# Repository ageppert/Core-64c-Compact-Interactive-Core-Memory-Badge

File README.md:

# Core-64c-Compact-Interactive-Core-Memory-Badge
Weave your own 64 bits of core memory over the top of LEDs to interact with directly using a magnetic wand.

Purchase: https://www.Core64.io

Follow this project at: https://hackaday.io/project/166155-core-64-interactive-core-memory-badge

You are in the hardware development repository. Production version firmware is at https://github.com/ageppert/Core64/

# Hardware Version History (latest on top)

HWV 0.3.0 Correct shift register schematic, add TC0_MON as ADC3, move 5V0 cap down, alternate LDO v-regs with 0.1uF caps, rotate SPI GPIO 180°, matrix current setting resistors 6.8 Ohm, I2C pull-ups 1.2K, add battery pack wire pads directly to board, silkscreen tweaks, move LED Matrix Driver components away from lanyard hole.

HWV 0.2.1 Rework HWV 0.2.0 to correct shift register schematics mistakes.

HWV 0.2.0 Change to 74HC595 shift registers for IO expansion. First version prototyped. Matrix current setting resistors 5.1 Ohm.

HWV 0.1.0 Compact Triple Stack - use 74HC138/238 3-to-8 decoders for IO expansion. Abandoned before prototyping.

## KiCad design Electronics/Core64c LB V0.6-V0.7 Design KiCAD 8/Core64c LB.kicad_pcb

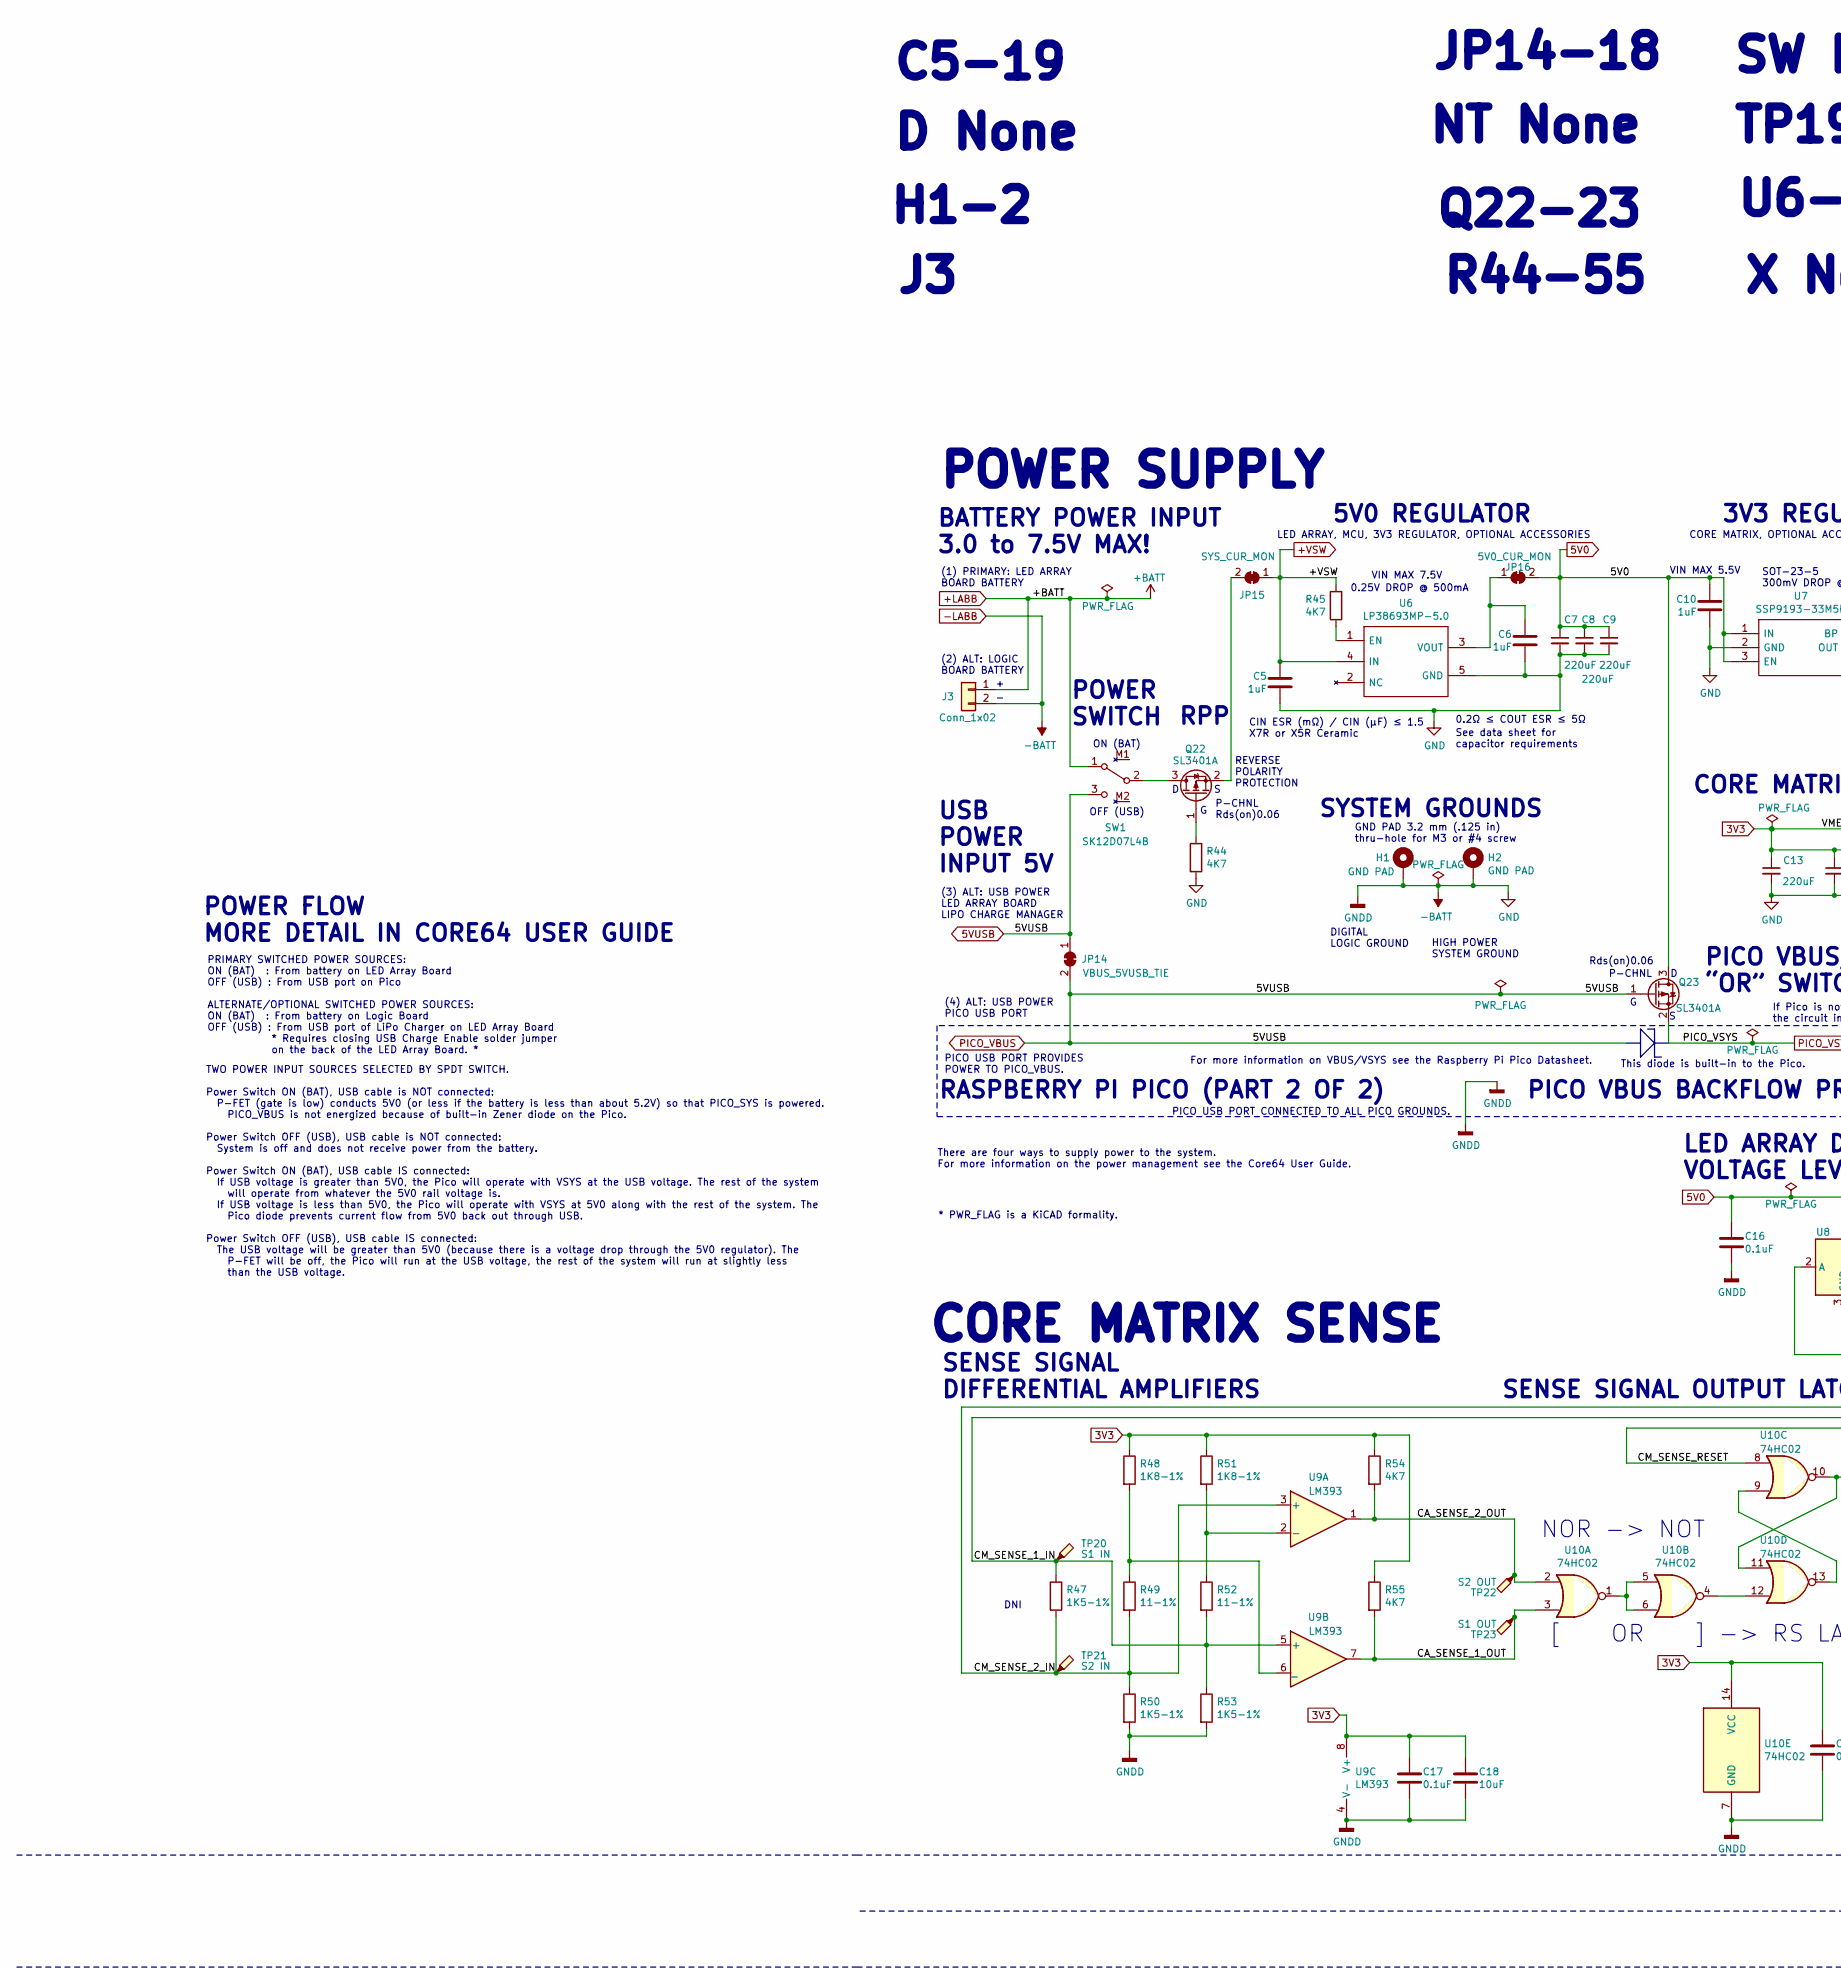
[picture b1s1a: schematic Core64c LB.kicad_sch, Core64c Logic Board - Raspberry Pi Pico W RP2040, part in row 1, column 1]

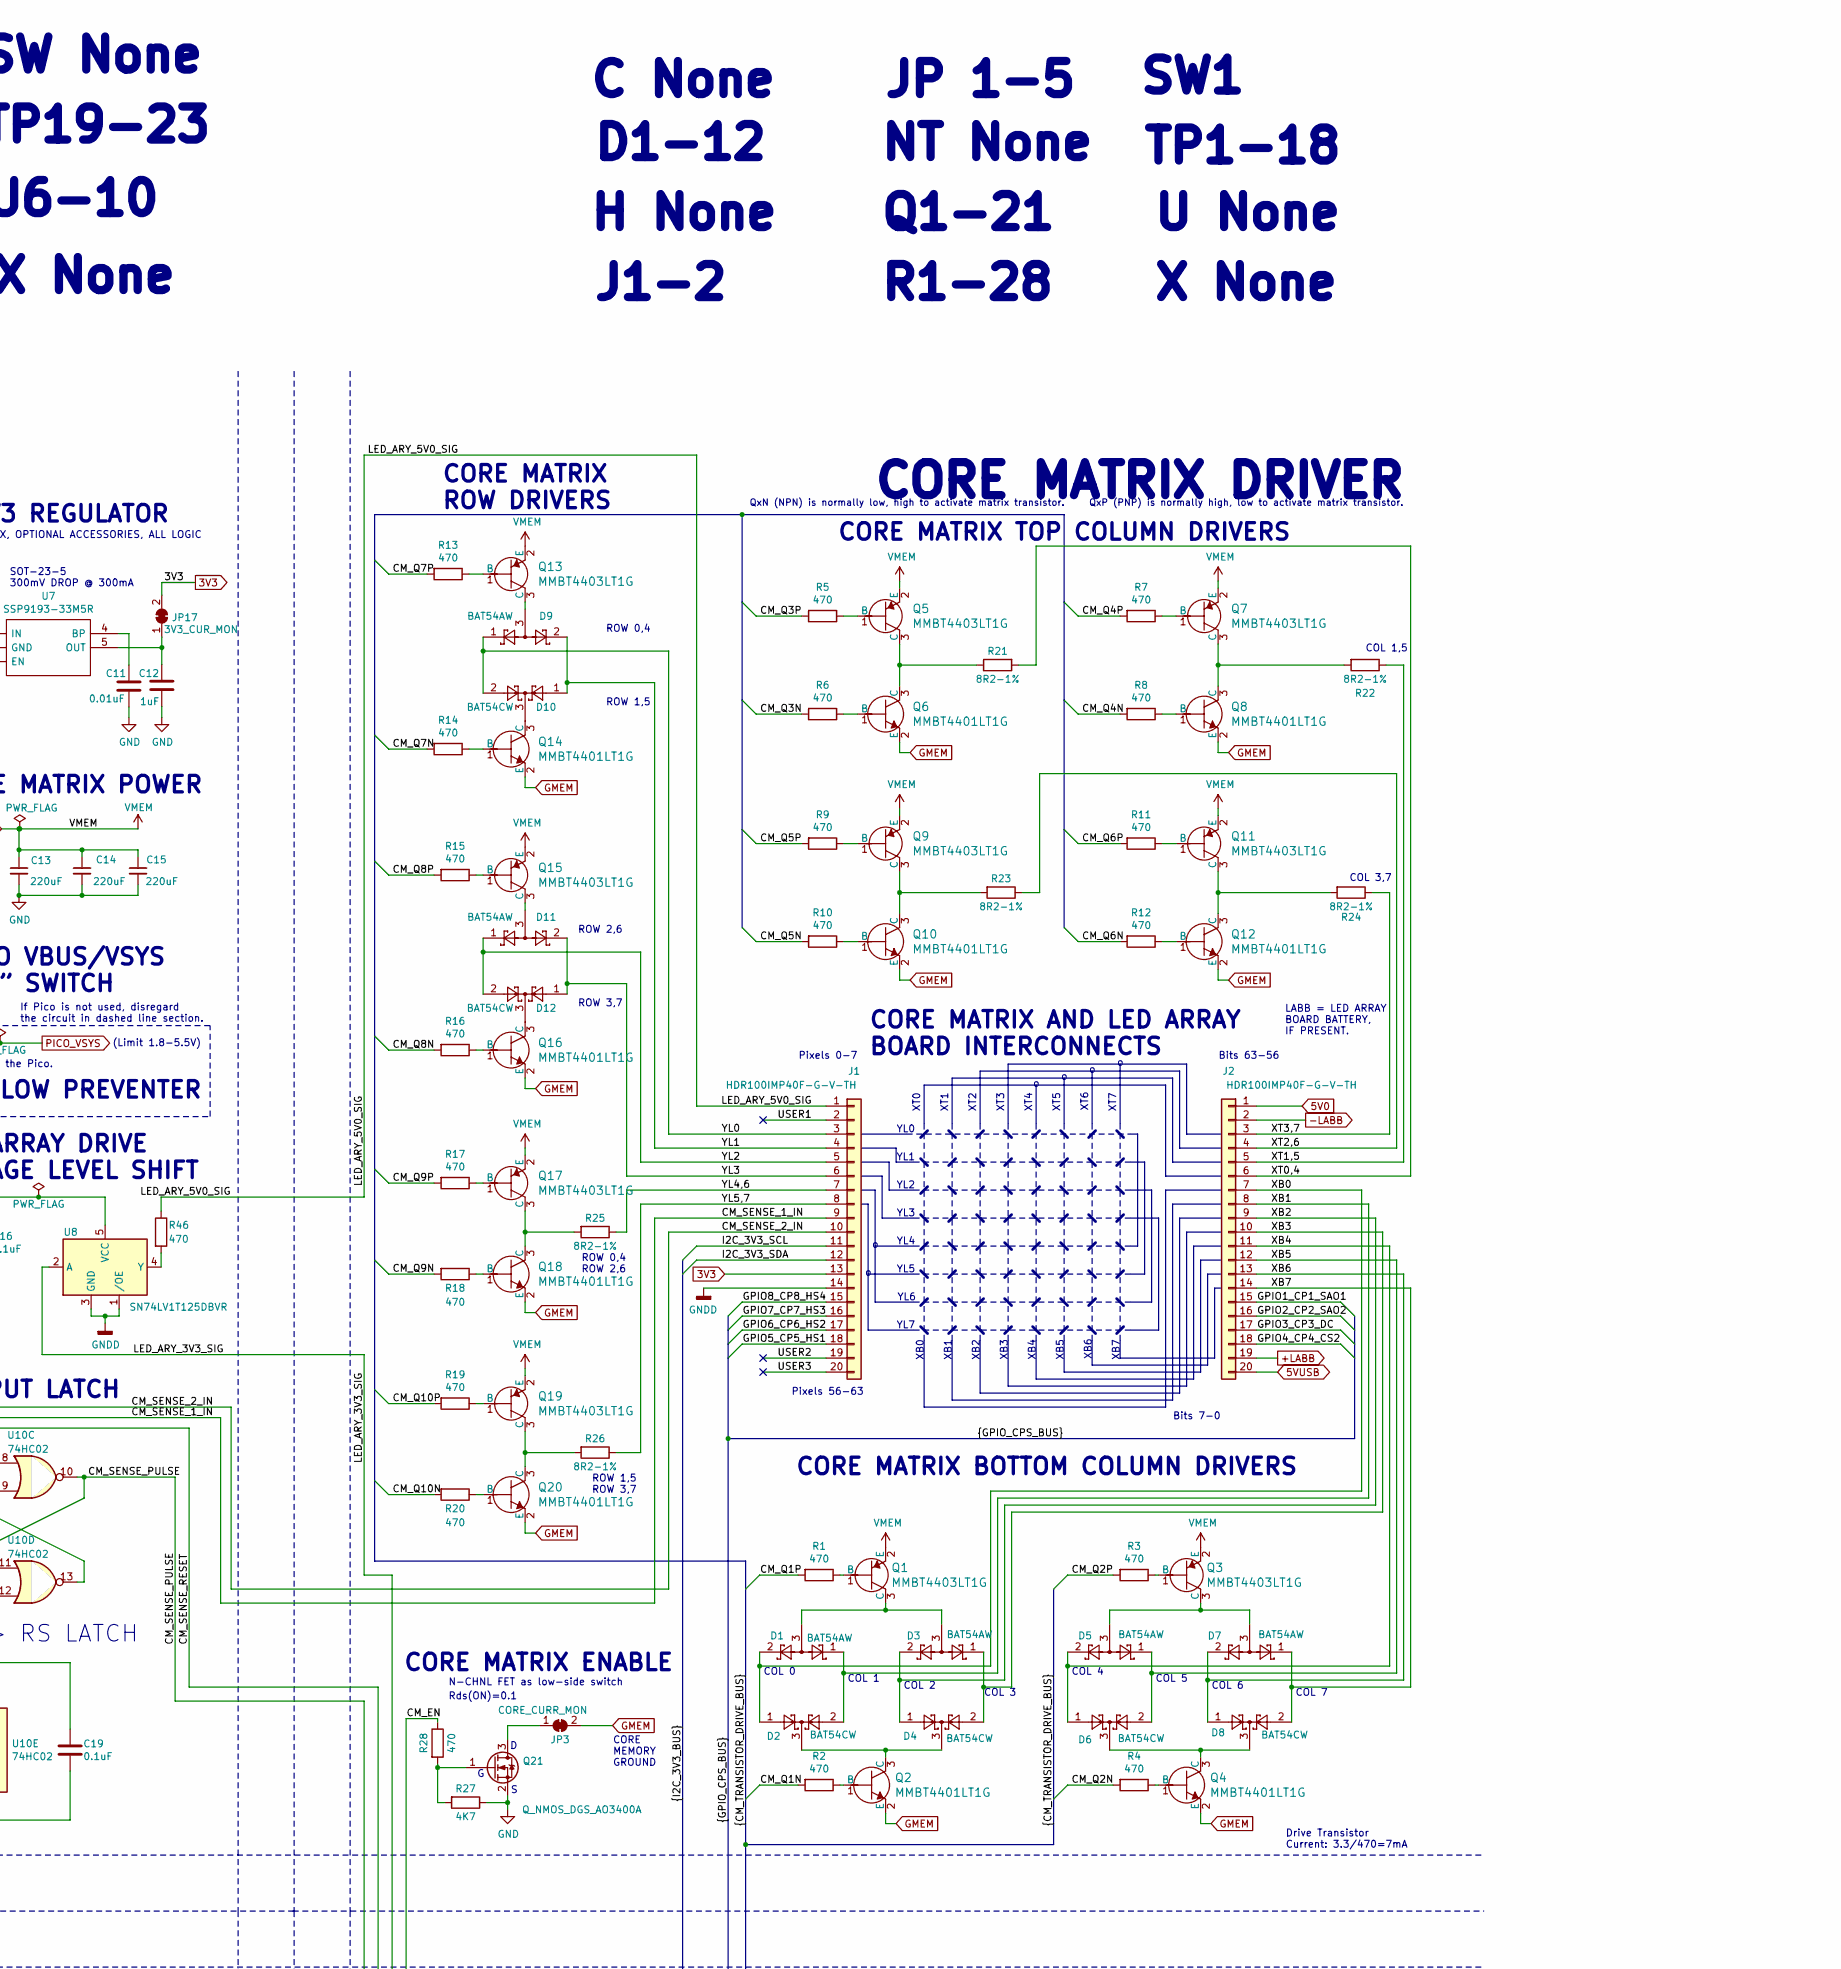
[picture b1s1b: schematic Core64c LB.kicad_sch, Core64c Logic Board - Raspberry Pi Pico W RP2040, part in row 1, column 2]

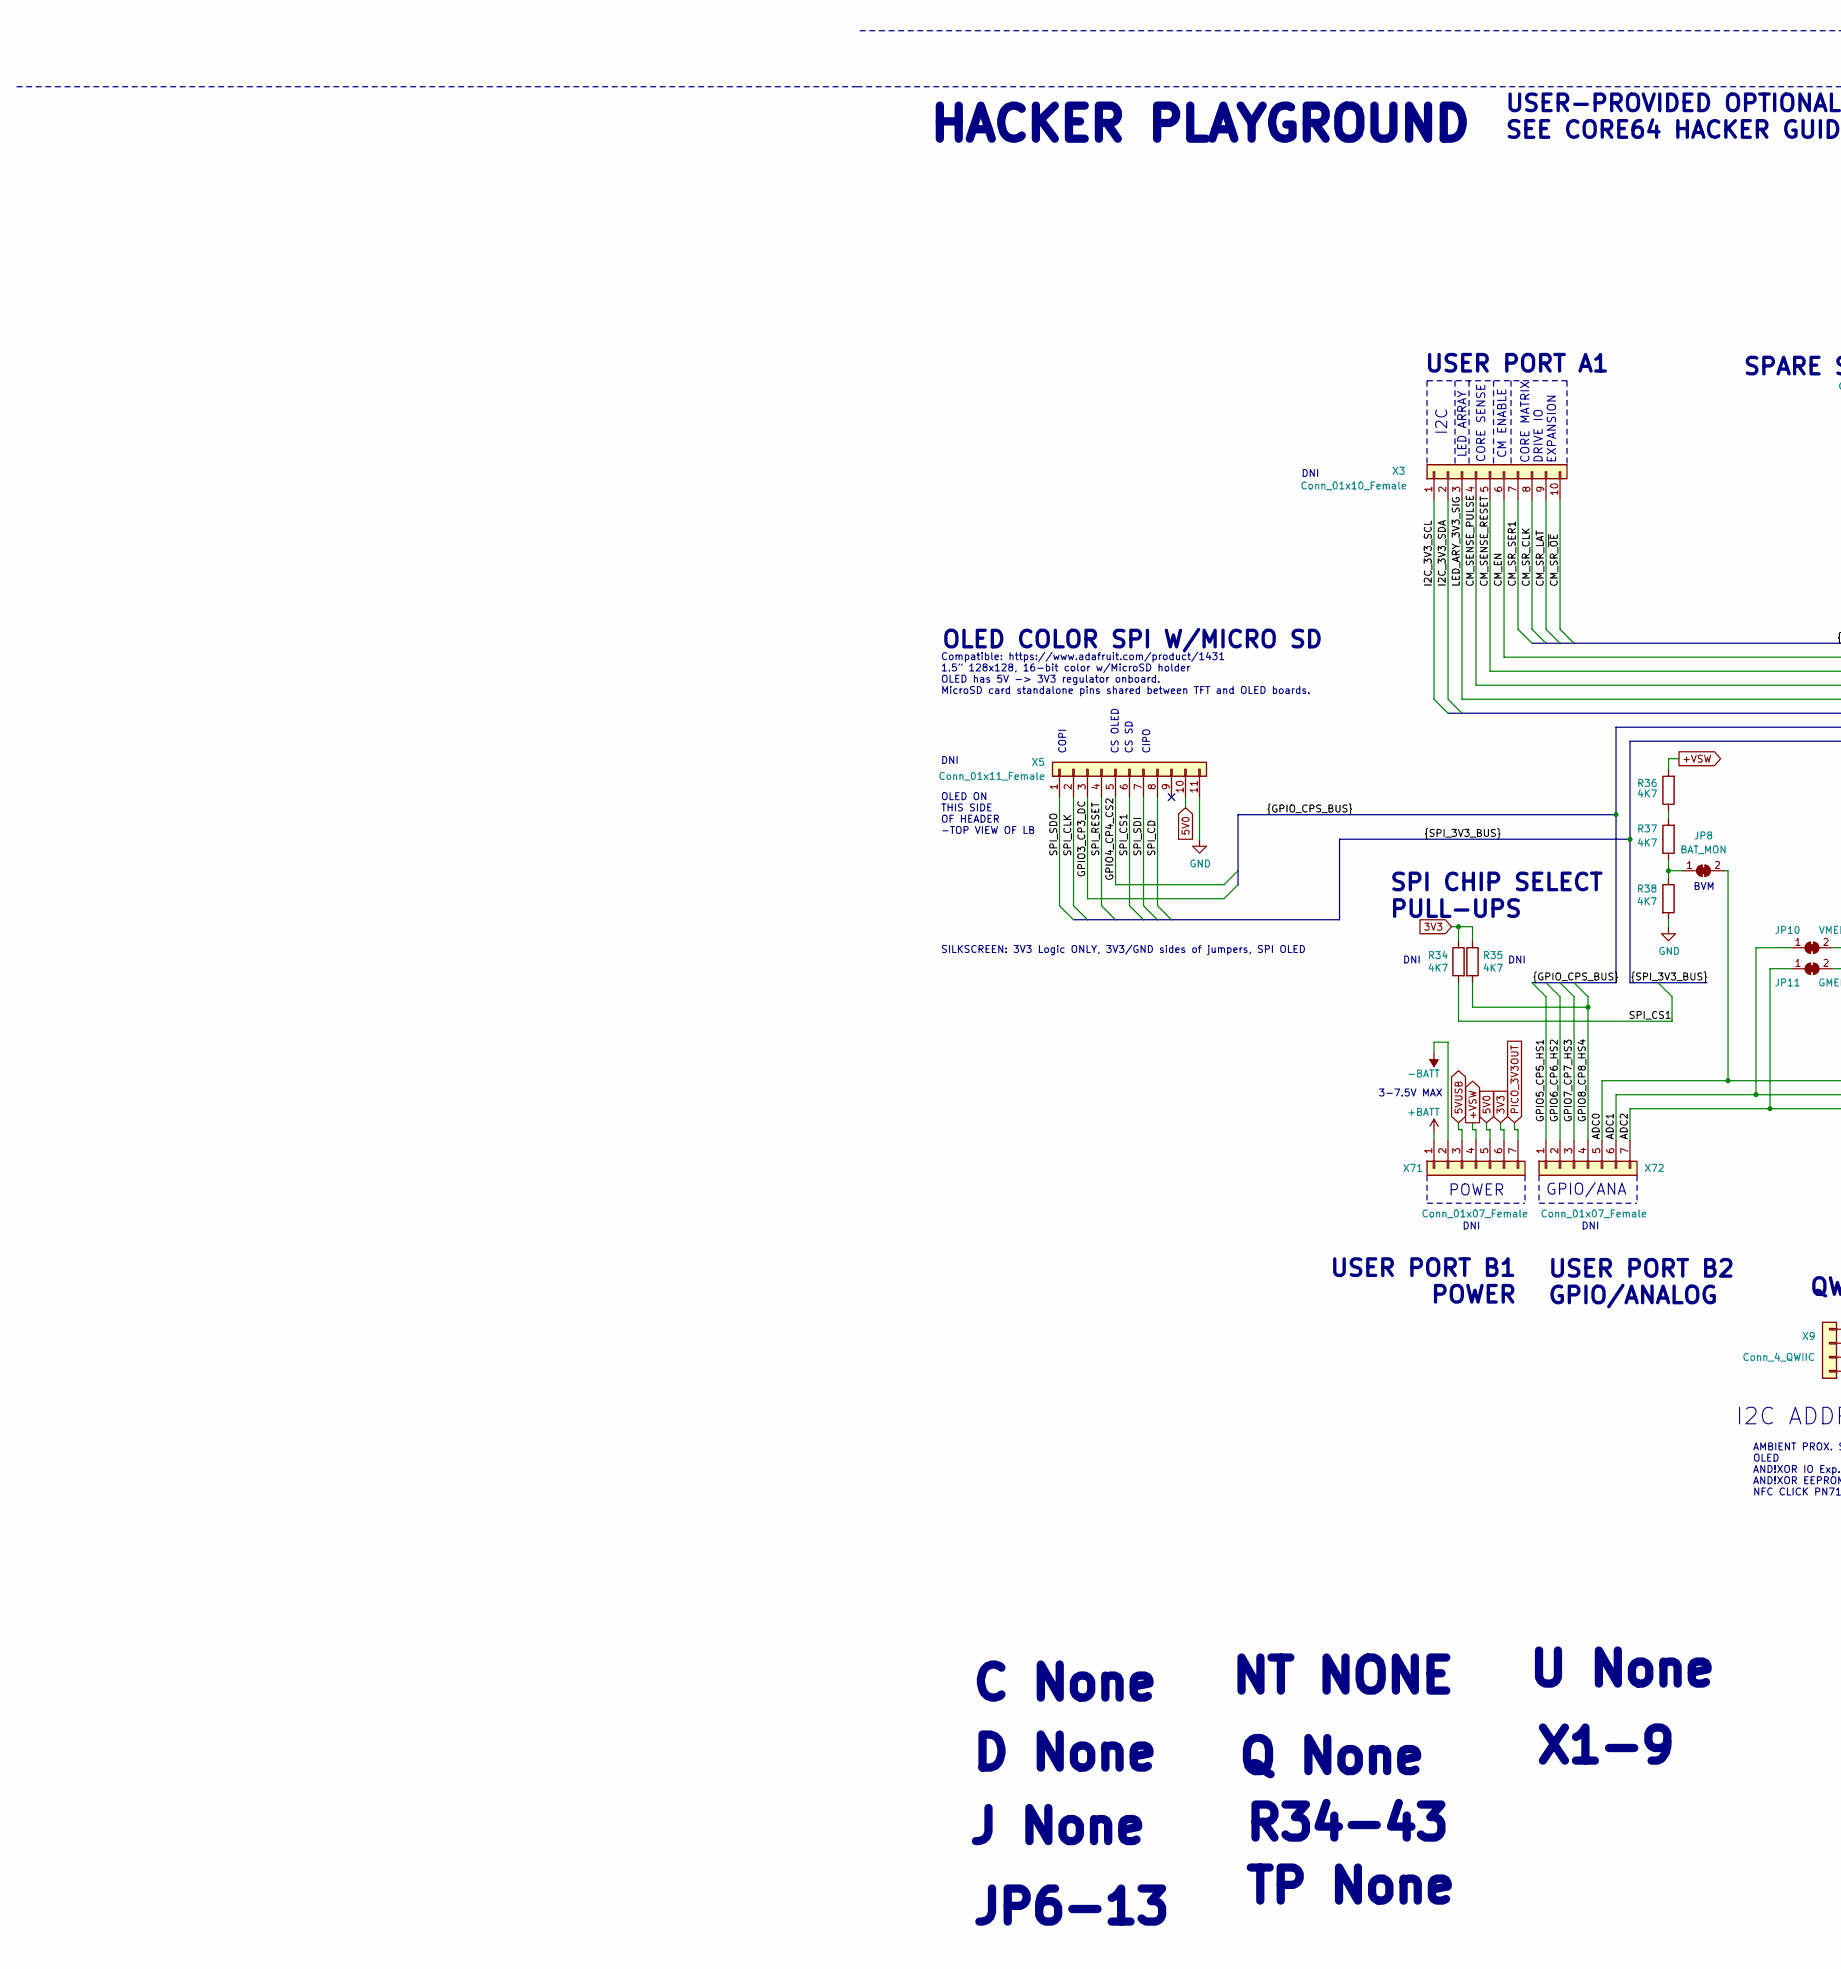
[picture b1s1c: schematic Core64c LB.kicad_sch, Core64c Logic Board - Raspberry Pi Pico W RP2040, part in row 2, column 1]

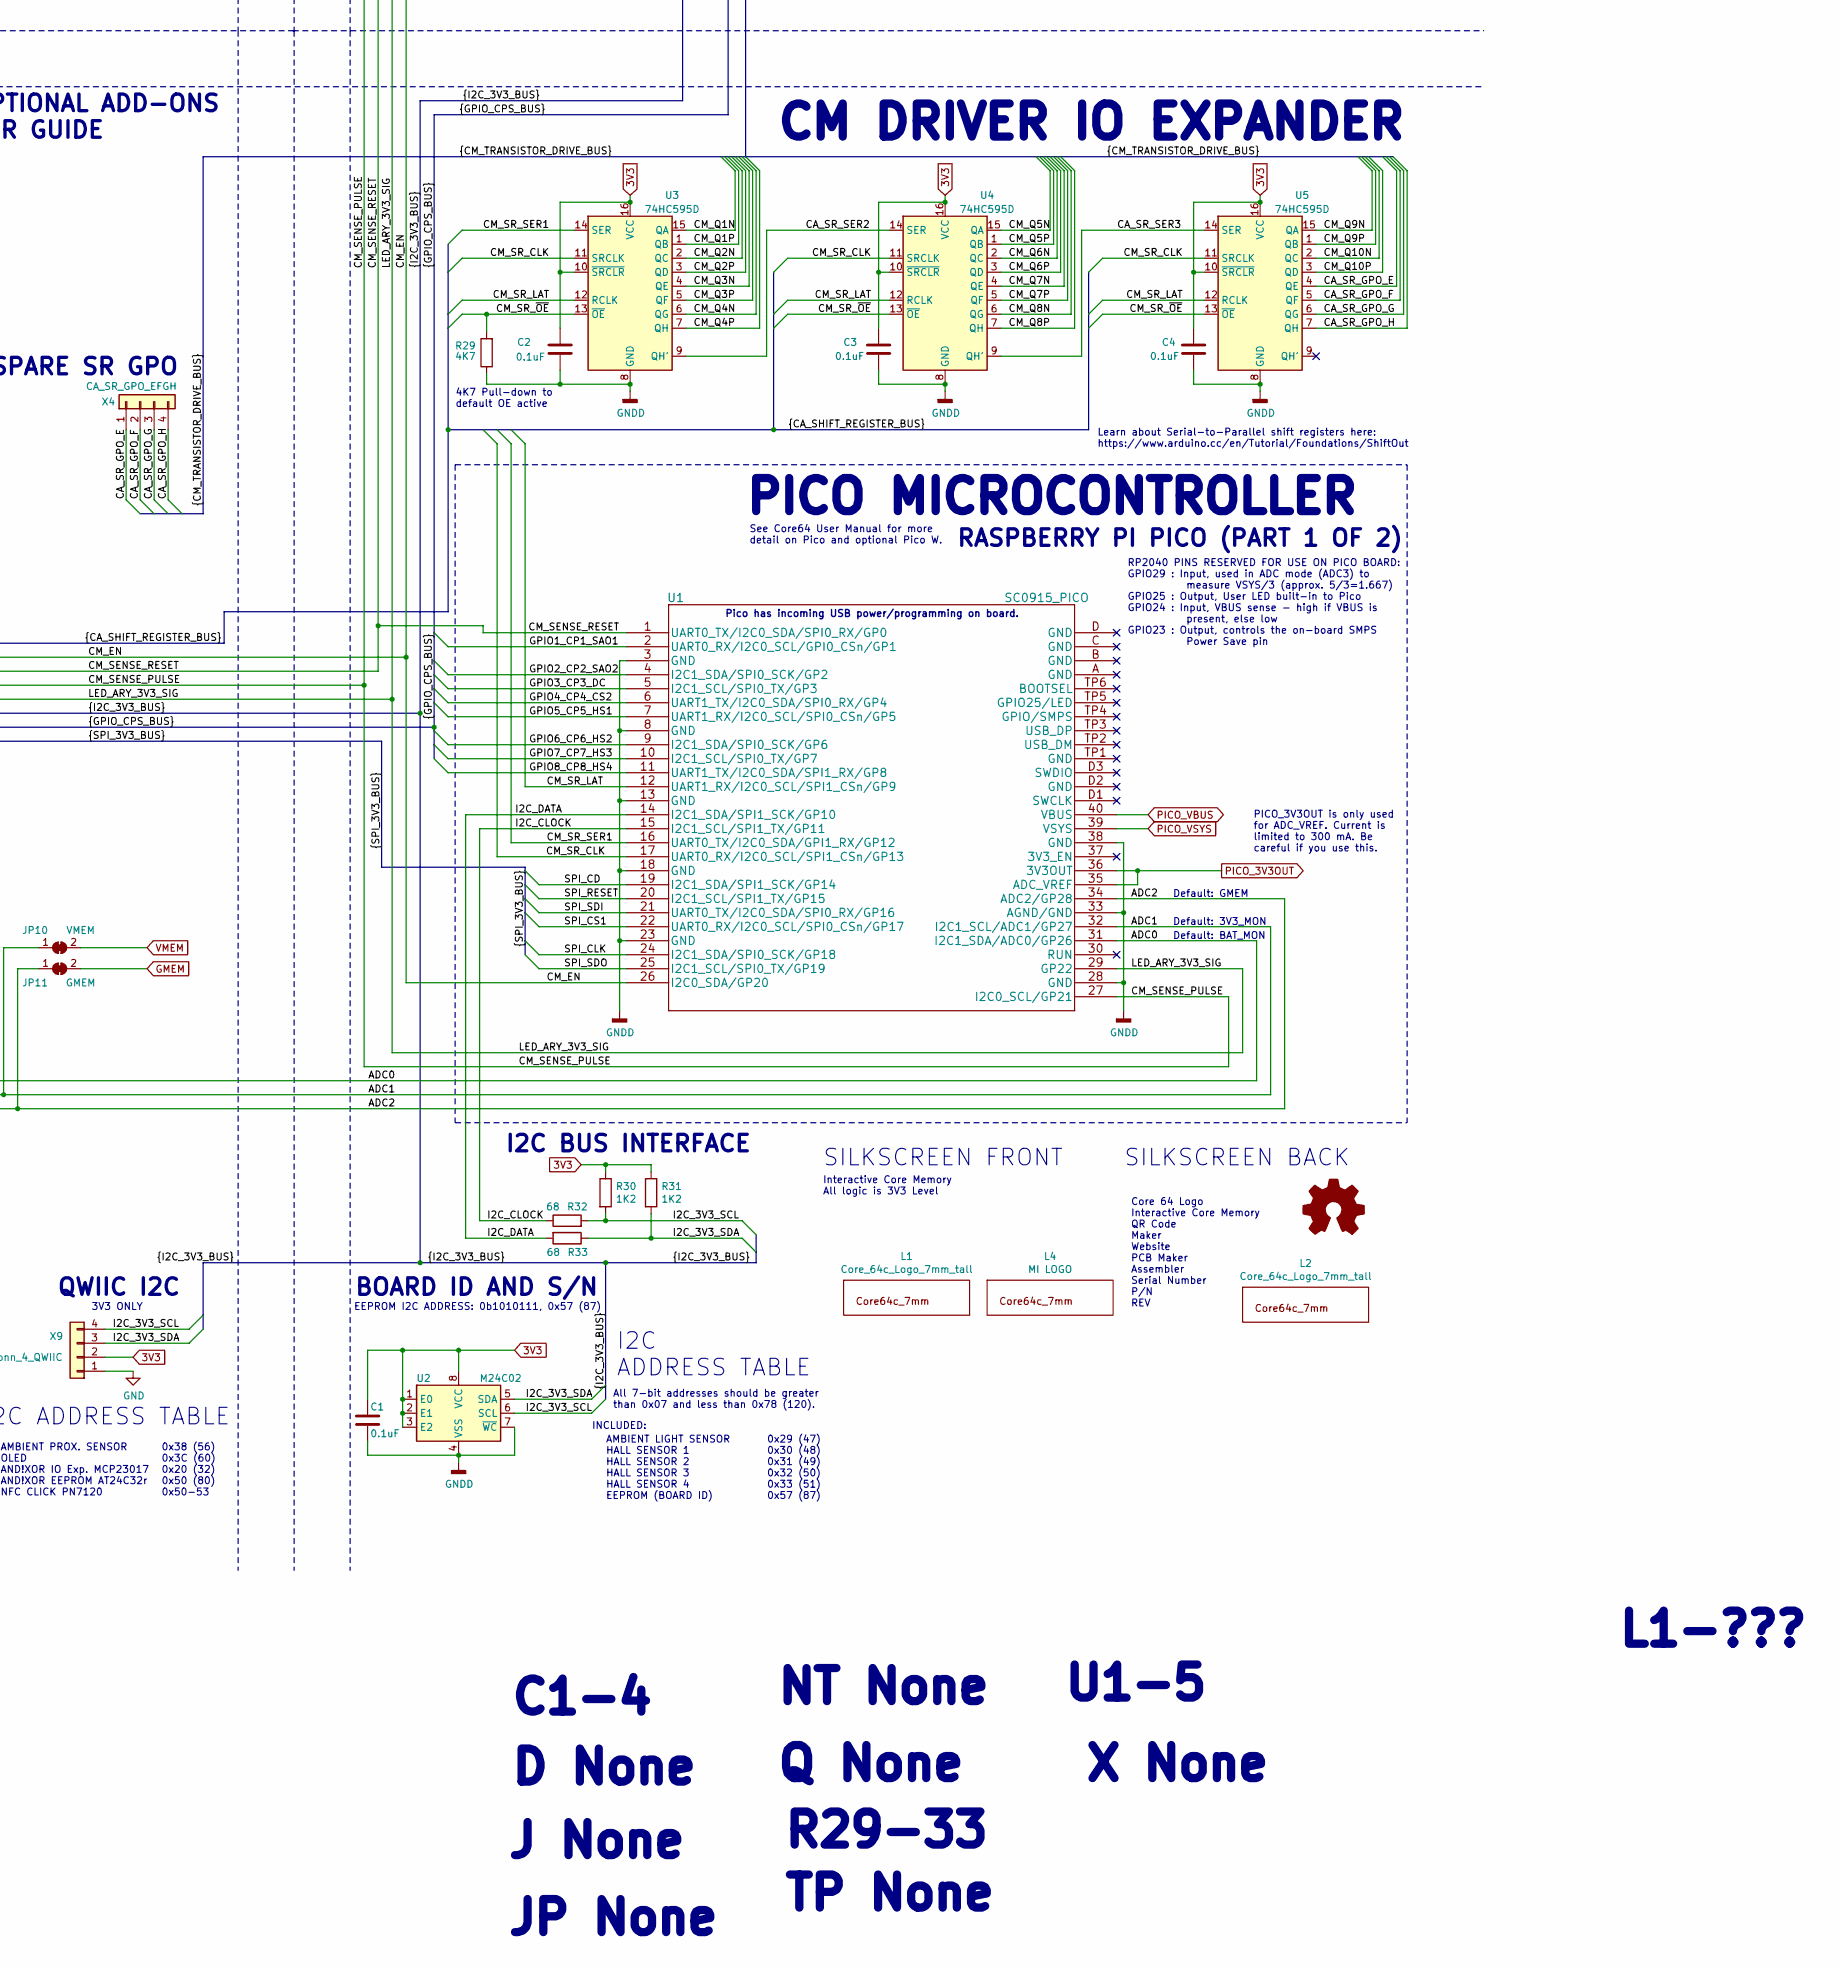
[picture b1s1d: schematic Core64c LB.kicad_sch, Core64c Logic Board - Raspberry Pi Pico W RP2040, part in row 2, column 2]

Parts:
C1, C2, C3, C4, C16, C17, C19: 0.1uF; C_0805_2012Metric; LCSC C28233
C5, C6, C10, C12: 1uF; C_0805_2012Metric; LCSC C28323
C7, C8, C9, C13, C14, C15: 220uF; C_1206_3216Metric; LCSC C412252
C11: 0.01uF; C_0805_2012Metric; LCSC C1710
C18: 10uF; C_0805_2012Metric; LCSC C17024
D1, D3, D5, D7, D9, D11: BAT54AW; SOT-323_SC-70; LCSC C78261
D2, D4, D6, D8, D10, D12: BAT54CW; SOT-323_SC-70; LCSC C83573
H1, H2: GND PAD; MountingHole_3.2mm_M3_Pad_Via
J1, J2: HDR100IMP40F-G-V-TH; PinSocket_1x20_P2.54mm_Vertical
J3: Conn_1x02; PinSocket_1x02_P2.54mm_Vertical
JP3: CORE_CURR_MON; SolderJumper-2_P1.3mm_Bridged_RoundedPad1.0x1.5mm
JP8: BAT_MON; SolderJumper-2_P1.3mm_Bridged_RoundedPad1.0x1.5mm
JP10: VMEM; SolderJumper-2_P1.3mm_Bridged_RoundedPad1.0x1.5mm
JP11: GMEM; SolderJumper-2_P1.3mm_Bridged_RoundedPad1.0x1.5mm
JP14: VBUS_5VUSB_TIE; SolderJumper-2_P1.3mm_Bridged_RoundedPad1.0x1.5mm
JP15: SYS_CUR_MON; SolderJumper-2_P1.3mm_Bridged_RoundedPad1.0x1.5mm
JP16: 5V0_CUR_MON; SolderJumper-2_P1.3mm_Bridged_RoundedPad1.0x1.5mm
JP17: 3V3_CUR_MON; SolderJumper-2_P1.3mm_Bridged_RoundedPad1.0x1.5mm
L1, L2: Core_64c_Logo_7mm_tall; Core64c_Logo_7mm
L3: Logo_Open_Hardware_Small; OSHW-Logo2_9.8x8mm_SilkScreen
L4: MI LOGO; Machine_Ideas_logo_1
Q1, Q3, Q5, Q7, Q9, Q11, Q13, Q15, Q17, Q19: MMBT4403LT1G; SOT-23-3; MPN MMBT4403LT1G; LCSC C78864
Q2, Q4, Q6, Q8, Q10, Q12, Q14, Q16, Q18, Q20: MMBT4401LT1G; SOT-23-3; MPN MMBT4401LT1G; LCSC C31776
Q21: Q_NMOS_DGS_AO3400A; SOT-23-3; LCSC C20917
Q22, Q23: SL3401A; SOT-23-3; LCSC C350311
R1, R2, R3, R4, R5, R6, R7, R8, R9, R10, R11, R12, R13, R14, R15, R16, R17, R18, R19, R20, R28, R46: 470; R_0805_2012Metric; LCSC C17710
R21, R22, R23, R24, R25, R26: 8R2-1%; R_0805_2012Metric; LCSC C17830
R27, R29, R34, R35, R36, R37, R38, R44, R45, R54, R55: 4K7; R_0805_2012Metric; LCSC C17673
R30, R31: 1K2; R_0805_2012Metric; LCSC C17379
R32, R33: 68; R_0805_2012Metric; LCSC C17802
R47, R50, R53: 1K5-1%; R_0805_2012Metric; LCSC C4310
R48, R51: 1K8-1%; R_0805_2012Metric; LCSC C17398
R49, R52: 11-1%; R_0805_2012Metric; LCSC C17430
SW1: SK12D07L4B; SK12D07VG4; LCSC C480340
TP20: S1 IN; TestPoint_THTPad_D1.5mm_Drill1.0mm
TP21: S2 IN; TestPoint_THTPad_D1.5mm_Drill1.0mm
TP22: S2 OUT; TestPoint_THTPad_D1.5mm_Drill1.0mm
TP23: S1 OUT; TestPoint_THTPad_D1.5mm_Drill1.0mm
U1: SC0915_PICO; Pico_W_SC0915
U2: M24C02; SOIC-8_3.9x4.9mm_P1.27mm; LCSC C7562
U3, U4, U5: 74HC595D; SOIC-16_W3.90mm; MPN SN74HC595DR; LCSC C5947
U6: LP38693MP-5.0; SOT-223-5; Manufacturer_Part_Number LP38693MP-5.0; Mouser Part Number LP38693MP-5.0
U7: SSP9193-33M5R; SOT-23-5; Manufacturer_Part_Number SGM2007-3.3XN5/TR; Mouser Part Number SGM2007-3.3XN5/TR
U8: SN74LV1T125DBVR; SOT-23-5; LCSC C473338
U9: LM393; SOIC-8_W3.9mm; LCSC C7955
U10: 74HC02; SOIC-14_3.9x8.7mm_P1.27mm; LCSC C350559
X3: Conn_01x10_Female; PinSocket_1x10_P2.54mm_Vertical
X4: CA_SR_GPO_EFGH; PinSocket_1x04_P2.54mm_Vertical
X5: Conn_01x11_Female; PinSocket_1x11_P2.54mm_Vertical
X9: Conn_4_QWIIC; JST_SH_SM04B-SRSS-TB_1x04-1MP_P1.00mm_Horizontal; MPN SM04B-SRSS-TB(LF)(SN); Digi-Key_PN 455-1804-1-ND
X71, X72: Conn_01x07_Female; PinSocket_1x07_P2.54mm_Vertical

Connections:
3V3: C1.1, C2.1, C3.1, C4.1, C13.1, C14.1, C15.1, C17.1, C18.1, C19.1, J1.13, JP10.2 (B), JP17.2 (B), Q1.2 (E), Q3.2 (E), Q5.2 (E), Q7.2 (E), Q9.2 (E), Q11.2 (E), Q13.2 (E), Q15.2 (E), Q17.2 (E), Q19.2 (E), R30.1, R31.1, R34.1, R35.1, R48.1, R51.1, R54.1, R55.1, U2.1 (E0), U2.2 (E1), U2.3 (E2), U2.8 (VCC), U3.10 (~SRCLR), U3.16 (VCC), U4.10 (~SRCLR), U4.16 (VCC), U5.10 (~SRCLR), U5.16 (VCC), U9.8 (V+), U10.14 (VCC), X9.2, X71.6
5V0: C7.1, C8.1, C9.1, C10.1, C16.1, J2.1, JP16.2 (B), Q23.3 (D), U7.1 (IN), U7.3 (EN), U8.5 (VCC), X5.10, X71.5
5VUSB: J2.20, JP14.1 (A), JP14.2 (B), Q23.1 (G), SW1.3 (C), U1.40 (VBUS), X71.3
+LABB: J2.19, J3.1, SW1.1 (A), X71.1
+VSW: C5.1, JP15.1 (A), R36.2, R45.1, U6.4 (IN), X71.4
-LABB: C1.2, C2.2, C3.2, C4.2, C5.2, C6.2, C7.2, C8.2, C9.2, C10.2, C11.2, C12.2, C13.2, C14.2, C15.2, C16.2, C17.2, C18.2, C19.2, H1.1, H2.1, J1.14, J2.2, J3.2, Q21.2 (S), R27.1, R29.1, R38.2, R44.2, R50.2, R53.2, U1.3 (GND), U1.8 (GND), U1.13 (GND), U1.18 (GND), U1.23 (GND), U1.28 (GND), U1.33 (AGND/GND), U1.38 (GND), U2.4 (VSS), U2.7 (~WC), U3.8 (GND), U4.8 (GND), U5.8 (GND), U6.5 (GND), U7.2 (GND), U8.1 (/OE), U8.3 (GND), U9.4 (V-), U10.7 (GND), X5.11, X9.1, X71.2
/ADC0: JP8.2 (B), U1.31 (I2C1_SDA/ADC0/GP26), X72.5
/ADC1: JP10.1 (A), U1.32 (I2C1_SCL/ADC1/GP27), X72.6
/ADC2: JP11.1 (A), U1.34 (ADC2/GP28), X72.7
/CA_SENSE_1_OUT: R55.2, TP23.1, U9.7, U10.3
/CA_SENSE_2_OUT: R54.2, TP22.1, U9.1, U10.2
/CA_SR_GPO_E: U5.4 (QE), X4.1
/CA_SR_GPO_F: U5.5 (QF), X4.2
/CA_SR_GPO_G: U5.6 (QG), X4.3
/CA_SR_GPO_H: U5.7 (QH), X4.4
/CA_SR_SER2: U3.9 (QH'), U4.14 (SER)
/CA_SR_SER3: U4.9 (QH'), U5.14 (SER)
/CM_EN: R28.1, U1.26 (I2C0_SDA/GP20), X3.6
/CM_Q1N: R2.2, U3.15 (QA)
/CM_Q1P: R1.2, U3.1 (QB)
/CM_Q2N: R4.2, U3.2 (QC)
/CM_Q2P: R3.2, U3.3 (QD)
/CM_Q3N: R6.2, U3.4 (QE)
/CM_Q3P: R5.2, U3.5 (QF)
/CM_Q4N: R8.2, U3.6 (QG)
/CM_Q4P: R7.2, U3.7 (QH)
/CM_Q5N: R10.2, U4.15 (QA)
/CM_Q5P: R9.2, U4.1 (QB)
/CM_Q6N: R12.2, U4.2 (QC)
/CM_Q6P: R11.2, U4.3 (QD)
/CM_Q7N: R14.2, U4.4 (QE)
/CM_Q7P: R13.2, U4.5 (QF)
/CM_Q8N: R16.2, U4.6 (QG)
/CM_Q8P: R15.2, U4.7 (QH)
/CM_Q9N: R18.2, U5.15 (QA)
/CM_Q9P: R17.2, U5.1 (QB)
/CM_Q10N: R20.2, U5.2 (QC)
/CM_Q10P: R19.2, U5.3 (QD)
/CM_SENSE_1_IN: J1.9, R47.1, R52.2, R53.1, TP20.1, U9.5 (+)
/CM_SENSE_2_IN: J1.10, R47.2, R49.2, R50.1, TP21.1, U9.3 (+)
/CM_SENSE_PULSE: U1.27 (I2C0_SCL/GP21), U10.10, U10.11, X3.4
/CM_SENSE_RESET: U1.1 (UART0_TX/I2C0_SDA/SPI0_RX/GP0), U10.8, X3.5
/CM_SR_CLK: U1.17 (UART0_RX/I2C0_SCL/SPI1_CSn/GP13), U3.11 (SRCLK), U4.11 (SRCLK), U5.11 (SRCLK), X3.8
/CM_SR_LAT: U1.12 (UART1_RX/I2C0_SCL/SPI1_CSn/GP9), U3.12 (RCLK), U4.12 (RCLK), U5.12 (RCLK), X3.9
/CM_SR_SER1: U1.16 (UART0_TX/I2C0_SDA/GPI1_RX/GP12), U3.14 (SER), X3.7
/CM_SR_~OE: R29.2, U3.13 (~OE), U4.13 (~OE), U5.13 (~OE), X3.10
/GPIO1_CP1_SAO1: J2.15, U1.2 (UART0_RX/I2C0_SCL/GPI0_CSn/GP1)
/GPIO2_CP2_SAO2: J2.16, U1.4 (I2C1_SDA/SPI0_SCK/GP2)
/GPIO3_CP3_DC: J2.17, U1.5 (I2C1_SCL/SPI0_TX/GP3), X5.3
/GPIO4_CP4_CS2: J2.18, U1.6 (UART1_TX/I2C0_SDA/SPI0_RX/GP4), X5.5
/GPIO5_CP5_HS1: J1.18, U1.7 (UART1_RX/I2C0_SCL/SPI0_CSn/GP5), X72.1
/GPIO6_CP6_HS2: J1.17, U1.9 (I2C1_SDA/SPI0_SCK/GP6), X72.2
/GPIO7_CP7_HS3: J1.16, U1.10 (I2C1_SCL/SPI0_TX/GP7), X72.3
/GPIO8_CP8_HS4: J1.15, R35.2, U1.11 (UART1_TX/I2C0_SDA/SPI1_RX/GP8), X72.4
/I2C_3V3_SCL: J1.11, R30.2, R32.2, U2.6 (SCL), X3.1, X9.4
/I2C_3V3_SDA: J1.12, R31.2, R33.1, U2.5 (SDA), X3.2, X9.3
/I2C_CLOCK: R32.1, U1.15 (I2C1_SCL/SPI1_TX/GP11)
/I2C_DATA: R33.2, U1.14 (I2C1_SDA/SPI1_SCK/GP10)
/LED_ARY_3V3_SIG: U1.29 (GP22), U8.2 (A), X3.3
/LED_ARY_5V0_SIG: J1.1, R46.1
/SPI_CD: U1.19 (I2C1_SDA/SPI1_SCK/GP14), X5.8
/SPI_CLK: U1.24 (I2C1_SDA/SPI0_SCK/GP18), X5.2
/SPI_CS1: R34.2, U1.22 (UART0_RX/I2C0_SCL/SPI0_CSn/GP17), X5.6
/SPI_RESET: U1.20 (I2C1_SCL/SPI1_TX/GP15), X5.4
/SPI_SDI: U1.21 (UART0_TX/I2C0_SDA/SPI0_RX/GP16), X5.7
/SPI_SDO: U1.25 (I2C1_SCL/SPI0_TX/GP19), X5.1
/USER1: J1.2
/USER2: J1.19
/USER3: J1.20
/XB0: D1.2, D2.1, J2.7
/XB1: D1.1, D2.2, J2.8
/XB2: D3.2, D4.1, J2.9
/XB3: D3.1, D4.2, J2.10
/XB4: D5.2, D6.1, J2.11
/XB5: D5.1, D6.2, J2.12
/XB6: D7.2, D8.1, J2.13
/XB7: D7.1, D8.2, J2.14
/XT0,4: J2.6, R21.2
/XT1,5: J2.5, R22.1
/XT2,6: J2.4, R23.1
/XT3,7: J2.3, R24.1
/YL0: D9.1, D10.2, J1.3
/YL1: D9.2, D10.1, J1.4
/YL2: D11.1, D12.2, J1.5
/YL3: D11.2, D12.1, J1.6
/YL4,6: J1.7, R25.1
/YL5,7: J1.8, R26.1
GMEM: JP3.2 (B), JP11.2 (B), Q2.2 (E), Q4.2 (E), Q6.2 (E), Q8.2 (E), Q10.2 (E), Q12.2 (E), Q14.2 (E), Q16.2 (E), Q18.2 (E), Q20.2 (E)
unnamed: JP3.1 (A), Q21.3 (D)
unnamed: JP8.1 (A), R37.1, R38.1
unnamed: JP15.2 (B), Q22.2 (S)
unnamed: C6.1, JP16.1 (A), U6.3 (VOUT)
unnamed: C12.1, JP17.1 (A), U7.5 (OUT)
unnamed: Q1.1 (B), R1.1
unnamed: D1.3, D3.3, Q1.3 (C)
unnamed: Q2.1 (B), R2.1
unnamed: D2.3, D4.3, Q2.3 (C)
unnamed: Q3.1 (B), R3.1
unnamed: D5.3, D7.3, Q3.3 (C)
unnamed: Q4.1 (B), R4.1
unnamed: D6.3, D8.3, Q4.3 (C)
unnamed: Q5.1 (B), R5.1
unnamed: Q5.3 (C), Q6.3 (C), R21.1
unnamed: Q6.1 (B), R6.1
unnamed: Q7.1 (B), R7.1
unnamed: Q7.3 (C), Q8.3 (C), R22.2
unnamed: Q8.1 (B), R8.1
unnamed: Q9.1 (B), R9.1
unnamed: Q10.1 (B), R10.1
unnamed: Q9.3 (C), Q10.3 (C), R23.2
unnamed: Q11.1 (B), R11.1
unnamed: Q11.3 (C), Q12.3 (C), R24.2
unnamed: Q12.1 (B), R12.1
unnamed: Q13.1 (B), R13.1
unnamed: D9.3, Q13.3 (C)
unnamed: Q14.1 (B), R14.1
unnamed: D10.3, Q14.3 (C)
unnamed: Q15.1 (B), R15.1
unnamed: D11.3, Q15.3 (C)
unnamed: Q16.1 (B), R16.1
unnamed: D12.3, Q16.3 (C)
unnamed: Q17.1 (B), R17.1
unnamed: Q17.3 (C), Q18.3 (C), R25.2
unnamed: Q18.1 (B), R18.1
unnamed: Q19.1 (B), R19.1
unnamed: Q19.3 (C), Q20.3 (C), R26.2
unnamed: Q20.1 (B), R20.1
unnamed: Q21.1 (G), R27.2, R28.2
unnamed: Q22.3 (D), SW1.2 (B)
unnamed: Q22.1 (G), R44.1
unnamed: R36.1, R37.2
unnamed: R45.2, U6.1 (EN)
unnamed: C11.1, U7.4 (BP)
unnamed: R46.2, U8.4 (Y)
unnamed: R51.2, R52.1, U9.2 (-)
unnamed: R48.2, R49.1, U9.6 (_)
unnamed: U10.1, U10.5, U10.6
unnamed: U10.4, U10.12
unnamed: U10.9, U10.13
PICO_3V3OUT: U1.35 (ADC_VREF), U1.36 (3V3OUT), X71.7
PICO_VSYS: Q23.2 (S), U1.39 (VSYS)

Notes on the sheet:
Bits 63-56
BATTERY POWER INPUT 3.0 to 7.5V MAX!
Pico has incoming USB power/programming on board.
SENSE SIGNAL OUTPUT LATCH
NT None
XT5
XT6
ROW 0,4
COL 3
YL4
3V3 REGULATOR
C None
NT NONE
SOT-23-5 300mV DROP @ 300mA
COL 1
TP None
HACKER PLAYGROUND
Default: GMEM
USER PORT B1 POWER
DNI
U None
SW1
ROW 1,5
PICO MICROCONTROLLER
PRIMARY SWITCHED POWER SOURCES: ON (BAT) : From battery on LED Array Board OFF (USB) : From USB port on Pico ALTERNATE/OPTIONAL SWITCHED POWER SOURCES: ON (BAT) : From battery on Logic Board OFF (USB) : From USB port of LiPo Charger on LED Array Board * Requires closing USB Charge Enable solder jum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
0x38 (56) 0x3C (60) 0x20 (32) 0x50 (80) 0x50-53
VIN MAX 5.5V
Bits 7-0
COL 1,5
N-CHNL FET as low-side switch
Rds(on)0.06
0.2Ω ≤ COUT ESR ≤ 5Ω
See Core64 User Manual for more detail on Pico and optional Pico W.
USER PORT B2 GPIO/ANALOG
0.25V DROP @ 500mA
CORE MATRIX, OPTIONAL ACCESSORIES, ALL LOGIC
LED ARRAY, MCU, 3V3 REGULATOR, OPTIONAL ACCESSORIES
OLED ON THIS SIDE OF HEADER -TOP VIEW OF LB
X None
Q None

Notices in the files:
parts and their libraries:
Copyright 2016 Accelerated Designs. All rights reserved.
